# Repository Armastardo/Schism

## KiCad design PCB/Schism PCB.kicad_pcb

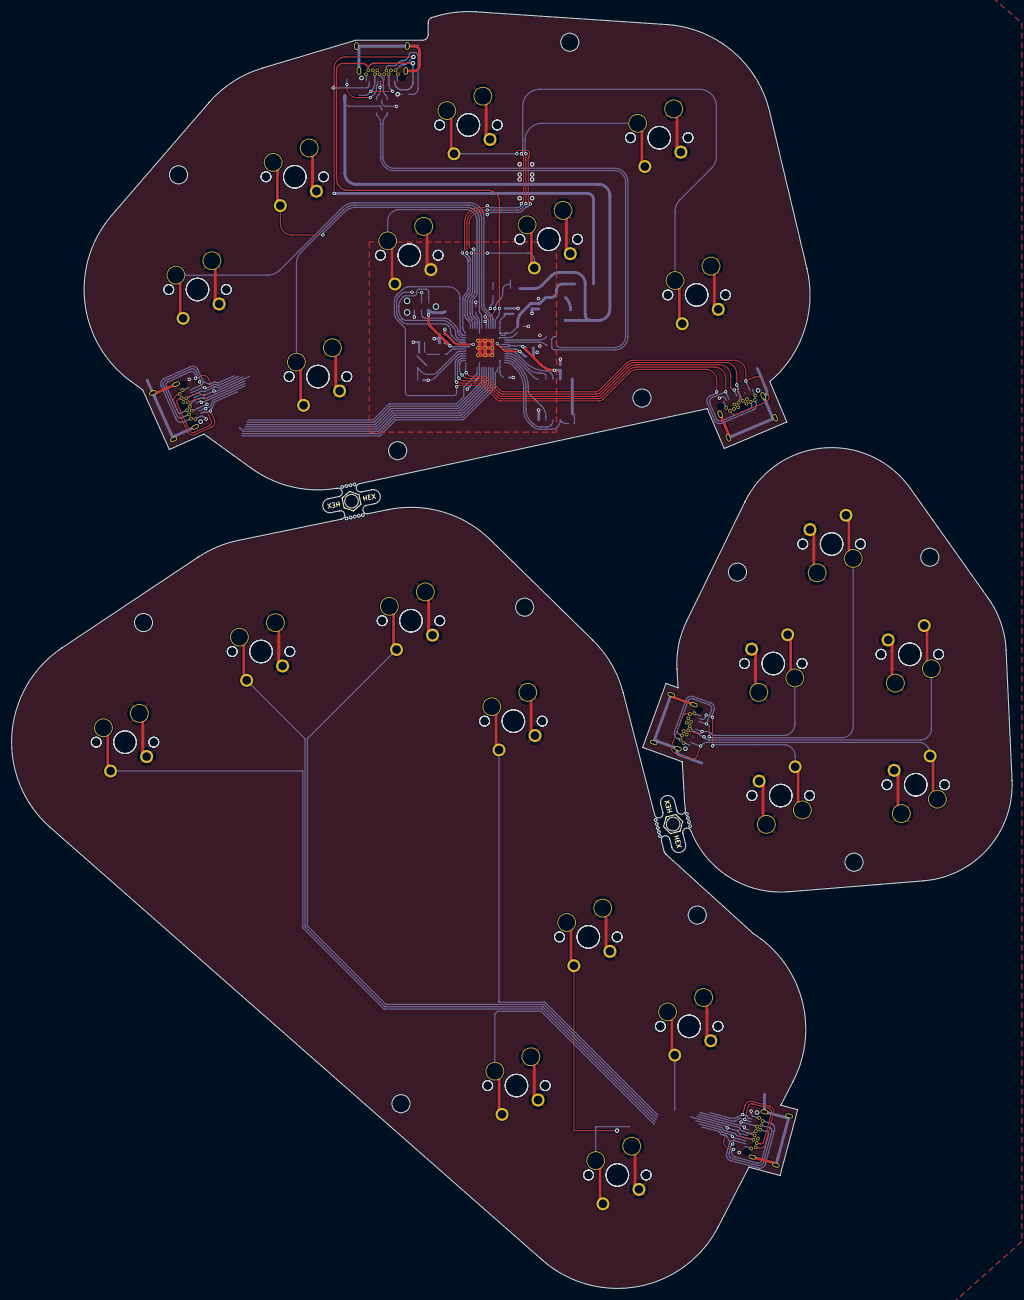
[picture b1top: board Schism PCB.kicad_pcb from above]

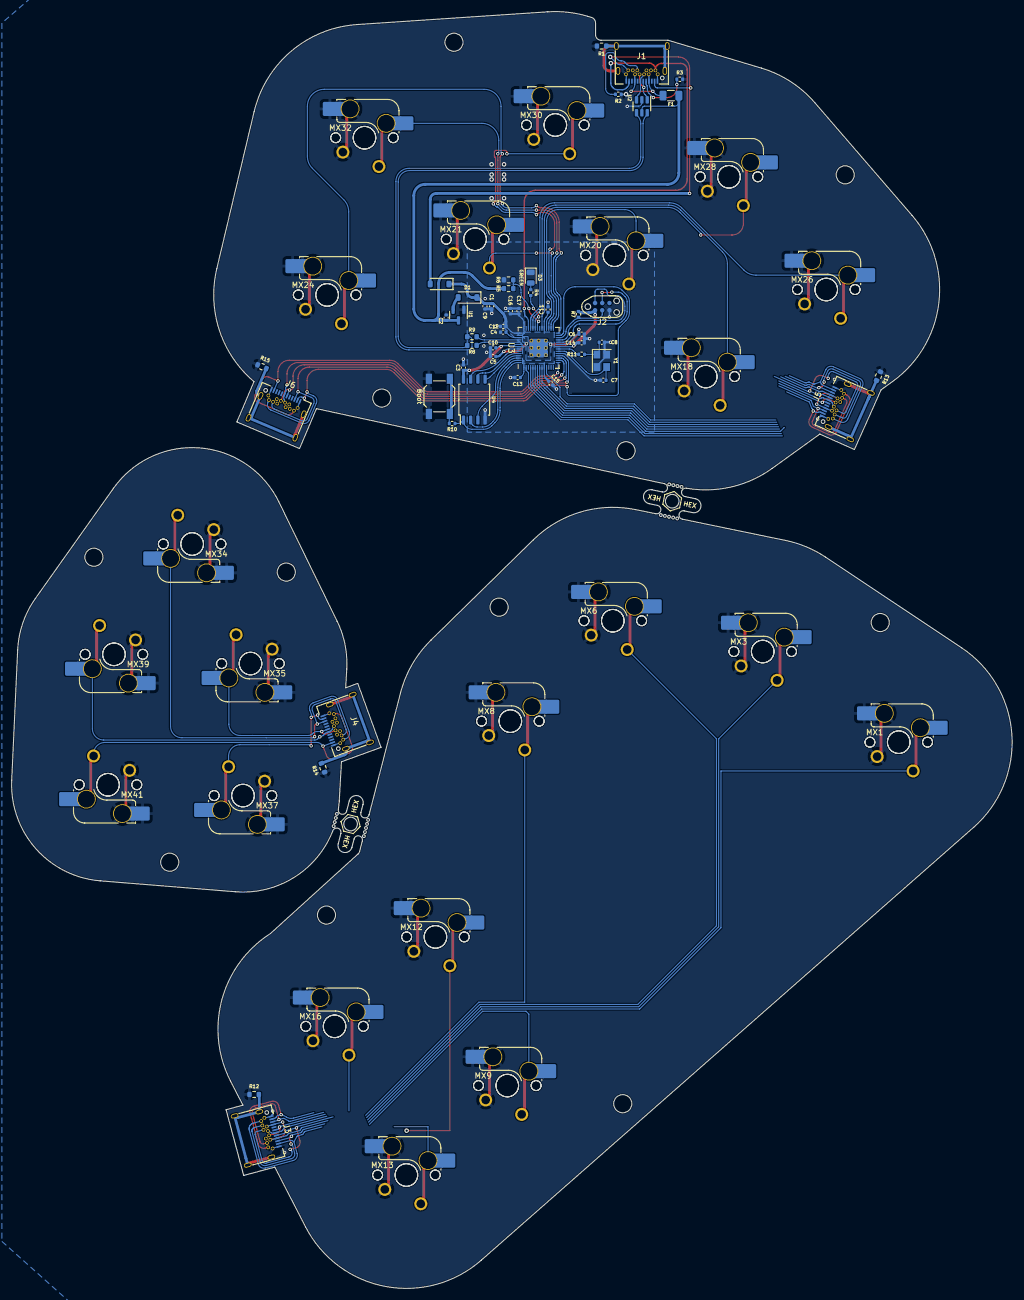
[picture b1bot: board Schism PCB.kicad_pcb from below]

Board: 2 copper layers, 176.5 x 225.2 mm, 92 parts (69 on the bottom side), 71 nets.

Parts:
C1, C2, C4, C10: 1uF; C_0402_1005Metric
C3, C5, C6, C11, C12, C13, C14, C15, C16, C17: 100nF; C_0402_1005Metric
C7, C8: 22pF; C_0402_1005Metric
C9: 10uF; C_0402_1005Metric
D1, D2: Schottky Diode; D_SOD-123
D3: GREEN; LED_0805_2012Metric
F1: 500 mA; Fuse_1206_3216Metric
J1, J3, J4, J5, J6: USB C Connector; TYPE-C_24P_QCHT
J2: JTAG_TC2030; CON_TC2030_outlined
MB5, MB6: MouseBites; mousebites_5p5mm_easysnap
MX1, MX3, MX6, MX8, MX9, MX12, MX13, MX16, MX18, MX20, MX21, MX24, MX26, MX28, MX30, MX32, MX34, MX35, MX37, MX39, MX41: MX_SW_HS; SW_MX_HS_1u
MX2, MX4, MX5, MX7, MX10, MX11, MX14, MX15, MX17, MX19, MX22, MX23, MX25, MX27, MX29, MX31, MX33, MX36, MX38, MX40, MX42: MX_SW_solder; SW_MX_1u
R1, R12, R13, R14, R15: 1M; R_0603_1608Metric
R2, R3: 5.1k; R_0402_1005Metric
R4, R7: 10k; R_0402_1005Metric
R5: 5.6k; R_0603_1608Metric
R6: 10k; R_0603_1608Metric
R8, R9: 27; R_0603_1608Metric
R10, R11: 1k; R_0402_1005Metric
SW1: Boot; SW_SPST_SKQG_WithStem
U1: XC6206; SOT-23
U2: USBLC6-2SC6; SOT-23-6
U3: RP2040; RP2040-QFN-56
U4: W25Q128JVS; SOIC-8_5.23x5.23mm_P1.27mm
Y1: 12MHz; Crystal_SMD_3225-4Pin_3.2x2.5mm

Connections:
3vCable: D2.2 (A), J1.A2 (TX1+), J1.B2 (TX2+)
+1V1: C4.1, C5.1, C6.1, U3.23 (DVDD), U3.45 (VREG_VOUT), U3.50 (DVDD)
+3V3: C1.2, C3.1, C9.1, C10.1, C11.1, C12.1, C13.1, C14.1, C15.1, C16.1, C17.1, D1.1 (K), D2.1 (K), J2.1 (VCC), R7.1, U3.1 (IOVDD), U3.10 (IOVDD), U3.22 (IOVDD), U3.33 (IOVDD), U3.42 (IOVDD), U3.43 (ADC_AVDD), U3.44 (VREG_VIN), U3.48 (USB_VDD), U3.49 (IOVDD), U4.8 (VCC)
+5V: C2.2, F1.2, R5.1, U1.3 (VI), U2.5 (VBUS)
/D_+: R8.2, U3.47 (D+)
/D_-: R9.2, U3.46 (D-)
/XTAL_O: C8.2, R11.1, Y1.1
/~USB_BOOT: R10.1, SW1.2
A: J6.A7 (D-), J6.B7 (D-), U3.17 (GPIO14)
A_2: J4.A7 (D-), J4.B7 (D-), MX35.1, MX36.2
B: MX17.2, MX18.1, U3.38 (GPIO26/ADC0)
CS: R10.2, U3.56 (QSPI_SS_N), U4.1 (~CS)
C_DN: J6.A10 (RX2-), J6.B10 (RX1-), U3.18 (GPIO15)
C_DN_2: J4.A10 (RX2-), J4.B10 (RX1-), MX33.2, MX34.1
C_LT: J6.A6 (D+), J6.B6 (D+), U3.16 (GPIO13)
C_LT_2: J4.A6 (D+), J4.B6 (D+), MX39.1, MX40.2
C_RT: J6.A11 (RX2+), J6.B11 (RX1+), U3.27 (GPIO16)
C_RT_2: J4.A11 (RX2+), J4.B11 (RX1+), MX37.1, MX38.2
C_UP: J6.A2 (TX1+), J6.B2 (TX2+), U3.15 (GPIO12)
C_UP_2: J4.A2 (TX1+), J4.B2 (TX2+), MX41.1, MX42.2
D+: R8.1, U2.6 (I/O1)
D-: R9.1, U2.4 (I/O2)
DATA: J1.A11 (RX2+), J1.B11 (RX1+), U3.40 (GPIO28/ADC2)
DBUS+: J1.A6 (D+), J1.B6 (D+), U2.1 (I/O1)
DBUS-: J1.A7 (D-), J1.B7 (D-), U2.3 (I/O2)
DOWN: J5.A6 (D+), J5.B6 (D+), U3.5 (GPIO3)
DOWN_2: J3.A6 (D+), J3.B6 (D+), MX5.2, MX6.1
GND: C1.1, C2.1, C3.2, C4.2, C5.2, C6.2, C7.1, C8.1, C9.2, C10.2, C11.2, C12.2, C13.2, C14.2, C15.2, C16.2, C17.2, D3.1 (K), J1.A1 (GND), J1.A12 (GND), J1.B1 (GND), J1.B12 (GND), J2.5 (GND), J3.A1 (GND), J3.A12 (GND), J3.B1 (GND), J3.B12 (GND), J4.A1 (GND), J4.A12 (GND), J4.B1 (GND), J4.B12 (GND), J5.A1 (GND), J5.A12 (GND), J5.B1 (GND), J5.B12 (GND), J6.A1 (GND), J6.A12 (GND), J6.B1 (GND), J6.B12 (GND), MX1.2, MX2.1, MX3.2, MX4.1, MX5.1, MX6.2, MX7.1, MX8.2, MX9.2, MX10.1, MX11.1, MX12.2, MX13.2, MX14.1, MX15.1, MX16.2, MX17.1, MX18.2, MX19.1, MX20.2, MX21.2, MX22.1, MX23.1, MX24.2, MX25.1, MX26.2, MX27.1, MX28.2, MX29.1, MX30.2, MX31.1, MX32.2, MX33.1, MX34.2, MX35.2, MX36.1, MX37.2, MX38.1, MX39.2, MX40.1, MX41.2, MX42.1, R1.1, R2.1, R3.2, R6.2, R12.1, R13.1, R14.1, R15.1, SW1.1, U1.1 (GND), U2.2 (GND), U3.19 (TESTEN), U3.57 (GND), U4.4 (GND), Y1.2, Y1.4
L: J5.A8 (SBU1), J5.B8 (SBU2), U3.7 (GPIO5)
LEFT: J5.A7 (D-), J5.B7 (D-), U3.6 (GPIO4)
LEFT_2: J3.A7 (D-), J3.B7 (D-), MX3.1, MX4.2
LS: MX29.2, MX30.1, U3.31 (GPIO20)
L_2: J3.A8 (SBU1), J3.B8 (SBU2), MX1.1, MX2.2
M1: J5.A4 (VBUS), J5.A9 (VBUS), J5.B4 (VBUS), J5.B9 (VBUS), U3.8 (GPIO6)
M1_2: J3.A4 (VBUS), J3.A9 (VBUS), J3.B4 (VBUS), J3.B9 (VBUS), MX9.1, MX10.2
M2: J5.A10 (RX2-), J5.B10 (RX1-), U3.9 (GPIO7)
M2_2: J3.A10 (RX2-), J3.B10 (RX1-), MX13.1, MX14.2
M3: J5.A11 (RX2+), J5.B11 (RX1+), U3.11 (GPIO8)
M3_2: J3.A11 (RX2+), J3.B11 (RX1+), MX11.2, MX12.1
MS: MX31.2, MX32.1, U3.29 (GPIO18)
unnamed: D1.2 (A), U1.2 (VO)
unnamed: D3.2 (A), R4.2
unnamed: F1.1, J1.A4 (VBUS), J1.A9 (VBUS), J1.B4 (VBUS), J1.B9 (VBUS)
unnamed: J1.A5 (CC1), R3.1
unnamed: J1.B5 (CC2), R2.2
unnamed: J1.S1 (SHIELD), R1.2
unnamed: J3.S1 (SHIELD), R12.2
unnamed: J4.S1 (SHIELD), R14.2
unnamed: J5.S1 (SHIELD), R13.2
unnamed: J6.S1 (SHIELD), R15.2
PICO_LED: R4.1, U3.37 (GPIO25)
QSPI_CLK: U3.52 (QSPI_SCLK), U4.6 (CLK)
R: MX25.2, MX26.1, U3.39 (GPIO27/ADC1)
RIGHT: J5.A3 (TX1-), J5.B3 (TX2-), U3.4 (GPIO2)
RIGHT_2: J3.A3 (TX1-), J3.B3 (TX2-), MX7.2, MX8.1
SD0: U3.53 (QSPI_SD0), U4.5 (DI(IO0))
SD1: U3.55 (QSPI_SD1), U4.2 (DO(IO1))
SD2: U3.54 (QSPI_SD2), U4.3 (IO2)
SD3: U3.51 (QSPI_SD3), U4.7 (IO3)
START: J5.A2 (TX1+), J5.B2 (TX2+), U3.2 (GPIO0)
START_2: J3.A2 (TX1+), J3.B2 (TX2+), MX15.2, MX16.1
SWCLK: J2.4 (SWCLK), U3.24 (SWCLK)
SWD: J2.2 (SWDIO), U3.25 (SWDIO)
UP: MX23.2, MX24.1, U3.28 (GPIO17)
VBUS_SENSE: R5.2, R6.1, U3.36 (GPIO24)
X: MX19.2, MX20.1, U3.32 (GPIO21)
XTAL_IN: C7.2, U3.20 (XTAL_IN), Y1.3
XTAL_OUT: R11.2, U3.21 (XTAL_OUT)
Y: MX27.2, MX28.1, U3.34 (GPIO22)
Z: MX21.1, MX22.2, U3.30 (GPIO19)
~RESET: J2.3 (~RST), R7.2, U3.26 (~RUN)

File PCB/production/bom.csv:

Designator,Footprint,Quantity,Value,LCSC Part #
"C1, C10, C2, C4",0402,4,1uF,C52923
"C11, C12, C13, C14, C15, C16, C17, C3, C5, C6",0402,10,100nF,C1525
"C7, C8",0402,2,22pF,C1555
C9,0402,1,10uF,C15525
"D1, D2",D_SOD-123,2,Schottky Diode,C8598
D3,0805,1,GREEN,C2297
F1,1206,1,500 mA,C70076
"J1, J3, J4, J5, J6",TYPE-C_24P_QCHT,5,USB C Connector,C456013
"MX1, MX12, MX13, MX16, MX18, MX20, MX21, MX24, MX26, MX28, MX3, MX30, MX32, MX34, MX35, MX37, MX39, MX41, MX6, MX8, MX9",SW_MX_HS_1u,21,MX_SW_HS,C2803348
"R1, R12, R13, R14, R15",0603,5,1M,C22935
"R10, R11",0402,2,1k,C11702
"R2, R3",0402,2,5.1k,C25744
"R4, R7",0402,2,10k,C25744
R5,0603,1,5.6k,C23189
R6,0603,1,10k,C25804
"R8, R9",0603,2,27,C25190
SW1,SW_SPST_SKQG_WithStem,1,Boot,C318884
U1,SOT-23,1,XC6206,C5446
U2,SOT-23-6,1,USBLC6-2SC6,C7519
U3,RP2040-QFN-56,1,RP2040,C2040
U4,SOIC-8_5.23x5.23mm_P1.27mm,1,W25Q128JVS,C97521
Y1,Crystal_SMD_3225-4Pin_3.2x2.5mm,1,12MHz,C9002

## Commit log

2023-10-24 Initial component placement and project setup
2023-10-25 Final schematic and component placement
2023-10-25 Almost done with the routing
2023-10-25 v0.1
2023-11-01 v0.1 choc version
2023-11-28 Revert "v0.1 choc version"
    This reverts commit 5703bf07c79f879200e349cafaf13ac2920e4a95.
2023-12-04 v0.3 electrically connected
2023-12-05 Pre-production files v0.3
2023-12-05 v0.3 i2c production
2024-01-24 v0.4
2024-02-21 v0.5
